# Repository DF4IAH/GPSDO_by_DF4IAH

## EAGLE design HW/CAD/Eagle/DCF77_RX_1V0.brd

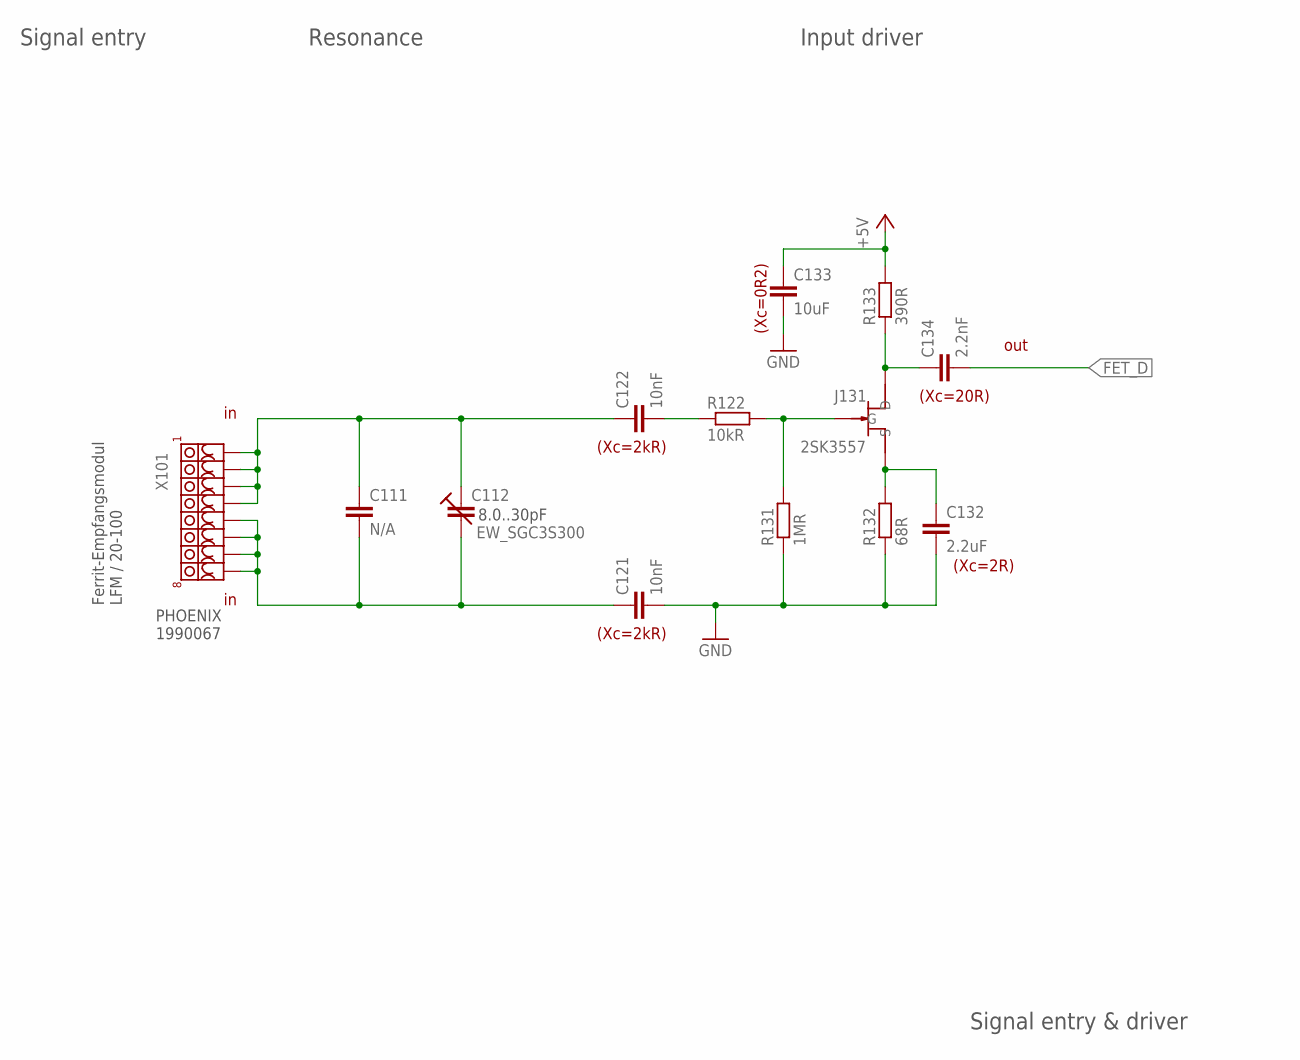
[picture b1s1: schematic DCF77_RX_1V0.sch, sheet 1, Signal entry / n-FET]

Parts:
C111: N/A; C0402
C112: EW_SGC3S300; 4MM5_X_3MM2__EW_SGC3S
C121, C122: 10nF; C0805
C132: 2.2uF; C0805
C133: 10uF; C0805
C134: 2.2nF; C0805
J131: 2SK3557; SOT23-3
R122: 10kR; R0805
R131: 1MR; R0805
R132: 68R; R0805
R133: 390R; R0805
X101: PHOENIX_1990067_1X8X2MM50_PTSA-0-5

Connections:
+5V: C133.1, R133.2; also elsewhere on the board
FET_D: C134.2; also elsewhere on the board
GND: C121.2, C132.2, C133.2, R131.1, R132.1; also elsewhere on the board
N101: C111.2, C112.CSTAT, C121.1, X101.5, X101.6, X101.7, X101.8
N102: C111.1, C112.CROT, C122.1, X101.1, X101.2, X101.3, X101.4
N122: C122.2, R122.1
N131: J131.P$3 (G), R122.2, R131.2
N132: C132.1, J131.P$1 (S), R132.2
N133: C134.1, J131.P$2 (D), R133.1

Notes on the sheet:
Signal entry & driver
Signal entry
out
Ferrit-Empfangsmodul LFM / 20-100
8.0..30pF
PHOENIX 1990067
Input driver
Resonance
(Xc=2R)
(Xc=20R)
(Xc=0R2)
(Xc=2kR)

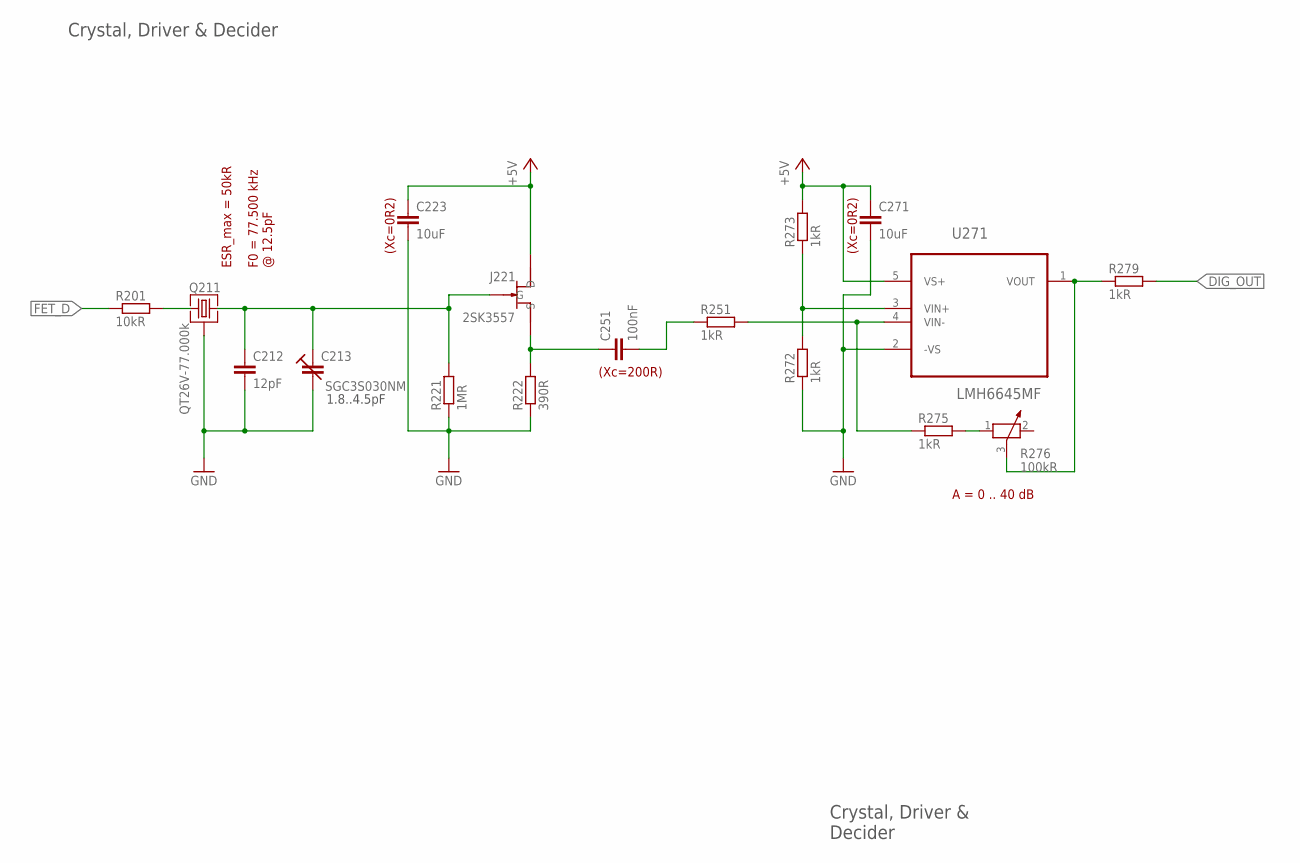
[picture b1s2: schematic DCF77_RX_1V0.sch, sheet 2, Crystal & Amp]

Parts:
C212: 12pF; C0402
C213: SGC3S030NM; 4MM5_X_3MM2__EW_SGC3S
C223, C271: 10uF; C0805
C251: 100nF; C0805
J221: 2SK3557; SOT23-3
Q211: QT26V-77.000k; QT26V_QST
R201: 10kR; R0805
R221: 1MR; R0805
R222: 390R; R0805
R251, R272, R273, R275, R279: 1kR; R0805
R276: 100kR; PT-10
U271: LMH6645MF; SOT-23-5

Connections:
+5V: C223.1, C271.1, J221.P$2 (D), R273.2, U271.5 (VS+); also elsewhere on the board
DIG_OUT: R279.2; also elsewhere on the board
FET_D: R201.1; also elsewhere on the board
GND: C212.2, C213.CSTAT, C223.2, C271.2, Q211.3, Q211.4 (3), R221.1, R222.1, R272.1, U271.2 (-VS); also elsewhere on the board
N211: Q211.1, R201.2
N221: C212.1, C213.CROT, J221.P$3 (G), Q211.2, R221.2
N222: C251.1, J221.P$1 (S), R222.2
N251: C251.2, R251.1
N271: R276.3, R279.1, U271.1 (VOUT)
N272: R272.2, R273.1, U271.3 (VIN+)
N273: R251.2, R275.1, U271.4 (VIN-)
N275: R275.2, R276.1

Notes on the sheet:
Crystal, Driver & Decider
1.8..4.5pF
Crystal, Driver & Decider
A = 0 .. 40 dB
ESR_max = 50kR
F0 = 77.500 kHz @ 12.5pF
(Xc=0R2)
(Xc=200R)

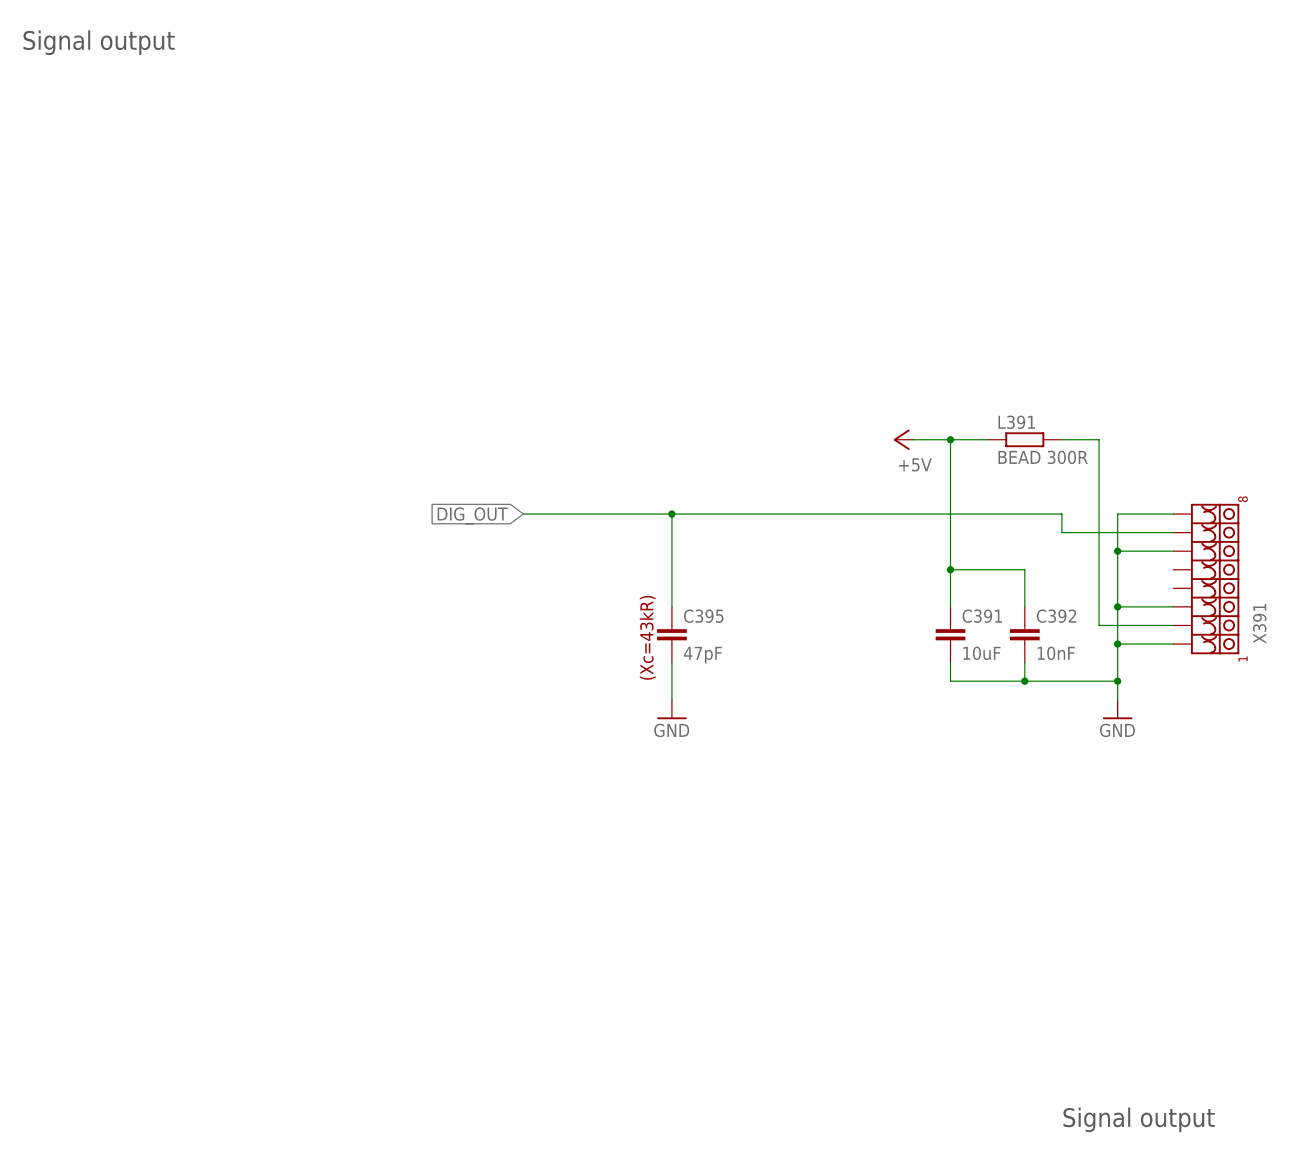
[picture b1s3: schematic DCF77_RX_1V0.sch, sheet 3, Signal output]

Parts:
C391: 10uF; C0805
C392: 10nF; C0805
C395: 47pF; C0805
L391: BEAD 300R; R1206
X391: PHOENIX_1990067_1X8X2MM50_PTSA-0-5

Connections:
+5V: C391.1, C392.1, L391.1; also elsewhere on the board
DIG_OUT: C395.1, X391.7; also elsewhere on the board
GND: C391.2, C392.2, C395.2, X391.1, X391.3, X391.6, X391.8; also elsewhere on the board
N391: L391.2, X391.2

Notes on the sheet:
Signal output
(Xc=43kR)

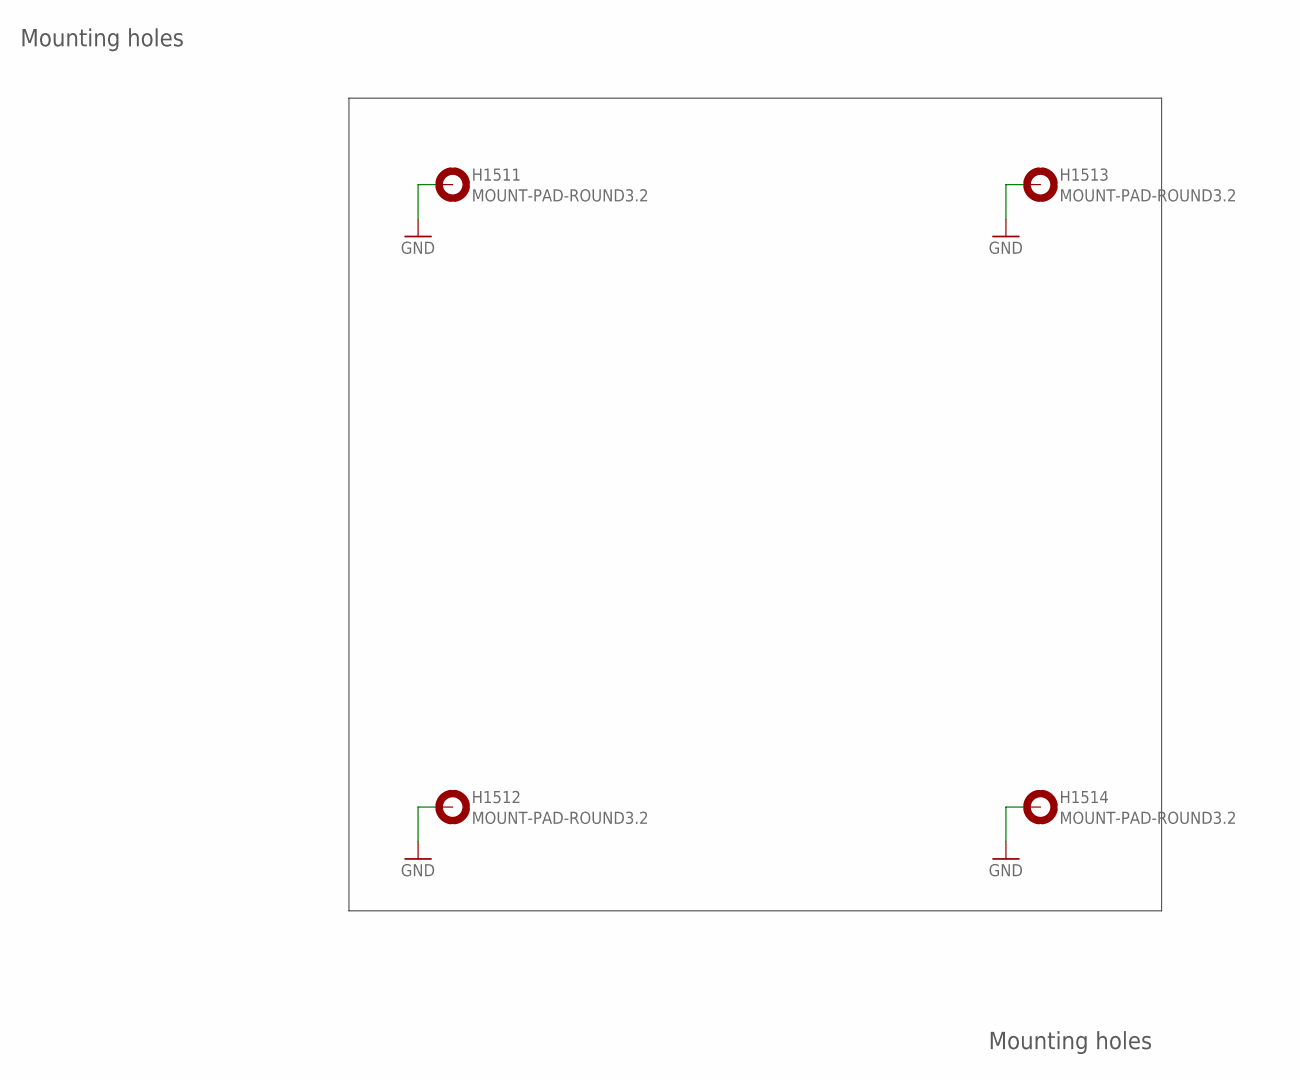
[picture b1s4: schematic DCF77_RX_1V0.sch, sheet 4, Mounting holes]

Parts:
H1511, H1512, H1513, H1514: MOUNT-PAD-ROUND3.2; 3,2-PAD

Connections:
GND: H1511.B3,2, H1512.B3,2, H1513.B3,2, H1514.B3,2; also elsewhere on the board

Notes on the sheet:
Mounting holes

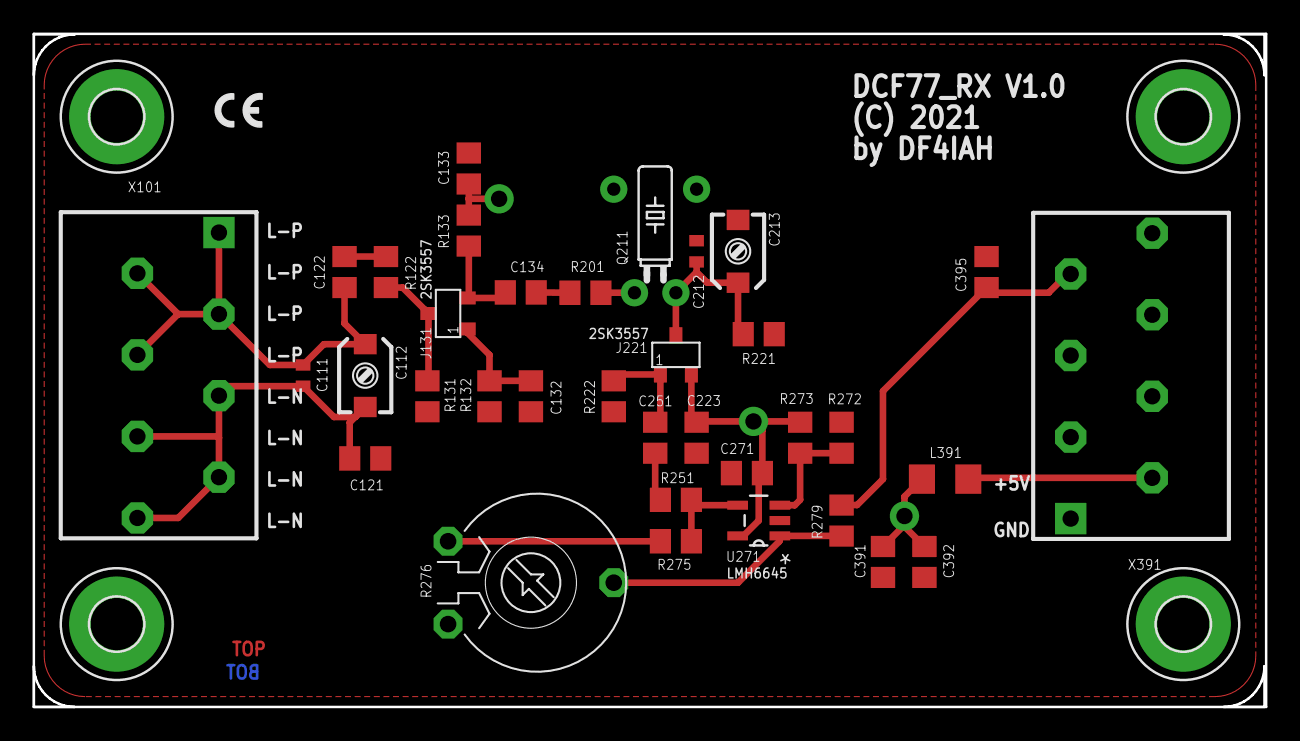
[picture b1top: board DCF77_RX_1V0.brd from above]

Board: 2 copper layers, 75.6 x 41.3 mm, 39 parts (0 on the bottom side), 19 nets.

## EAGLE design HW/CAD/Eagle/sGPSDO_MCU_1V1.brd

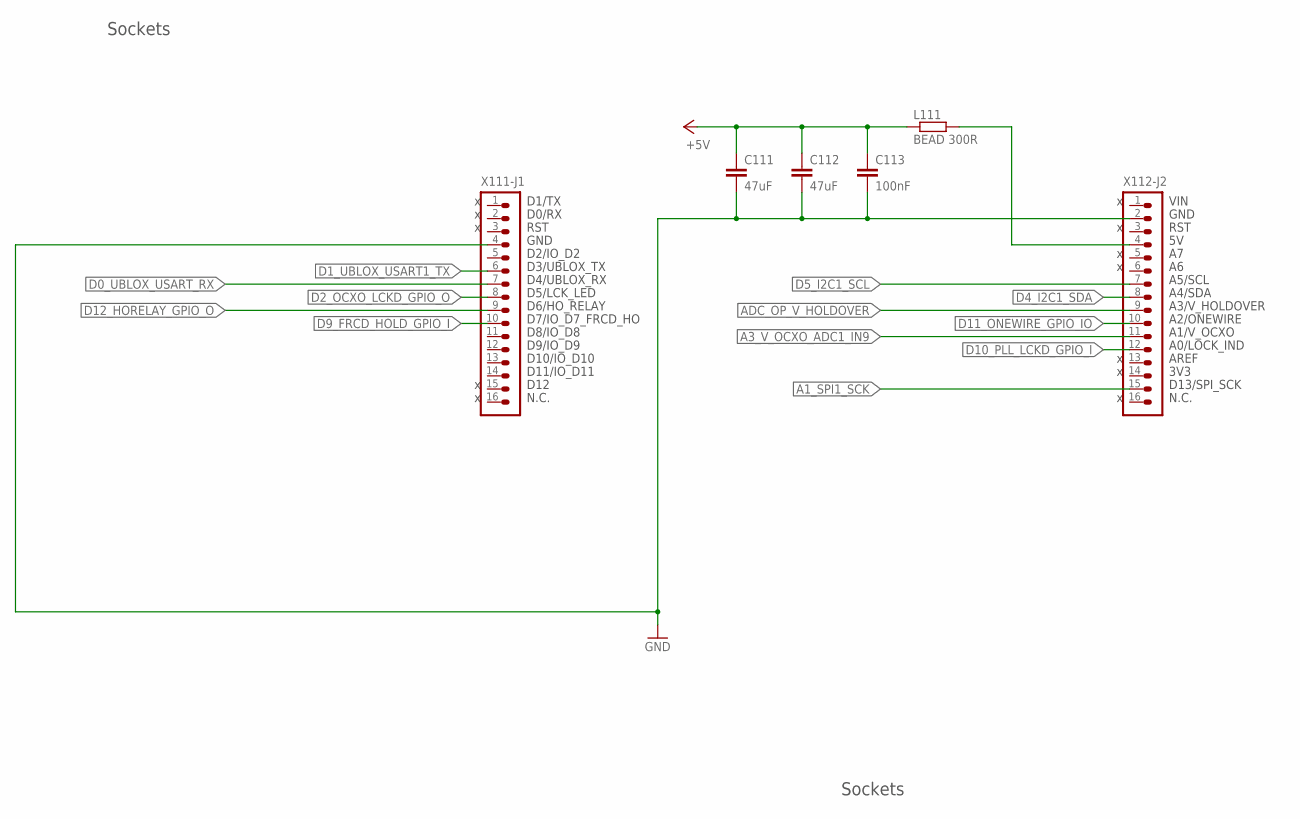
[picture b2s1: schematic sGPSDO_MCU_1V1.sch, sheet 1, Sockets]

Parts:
C111, C112: 47uF; C0805
C113: 100nF; C0805
L111: BEAD 300R; R1206
X111-J1, X112-J2: HEADER-1X16; 1X16

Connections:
+5V: C111.1, C112.1, C113.1, L111.1; also elsewhere on the board
A1_SPI1_SCK: X112-J2.15; also elsewhere on the board
A3_V_OCXO_ADC1_IN9: X112-J2.11; also elsewhere on the board
ADC_OP_V_HOLDOVER: X112-J2.9; also elsewhere on the board
D0_UBLOX_USART_RX: X111-J1.7; also elsewhere on the board
D1_UBLOX_USART1_TX: X111-J1.6; also elsewhere on the board
D2_OCXO_LCKD_GPIO_O: X111-J1.8; also elsewhere on the board
D4_I2C1_SDA: X112-J2.8; also elsewhere on the board
D5_I2C1_SCL: X112-J2.7; also elsewhere on the board
D9_FRCD_HOLD_GPIO_I: X111-J1.10; also elsewhere on the board
D10_PLL_LCKD_GPIO_I: X112-J2.12; also elsewhere on the board
D11_ONEWIRE_GPIO_IO: X112-J2.10; also elsewhere on the board
D12_HORELAY_GPIO_O: X111-J1.9; also elsewhere on the board
GND: C111.2, C112.2, C113.2, X111-J1.4, X112-J2.2; also elsewhere on the board
N112: L111.2, X112-J2.4

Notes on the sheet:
Sockets
A0/LOCK_IND
AREF
3V3
D13/SPI_SCK
N.C.
A1/V_OCXO
A2/ONEWIRE
A3/V_HOLDOVER
A4/SDA
A5/SCL
RST
GND
VIN
D12
D11/IO_D11
D10/IO_D10
D9/IO_D9
D8/IO_D8
D7/IO_D7_FRCD_HO
D6/HO_RELAY
D5/LCK_LED
D4/UBLOX_RX
D3/UBLOX_TX
D2/IO_D2
D0/RX
D1/TX

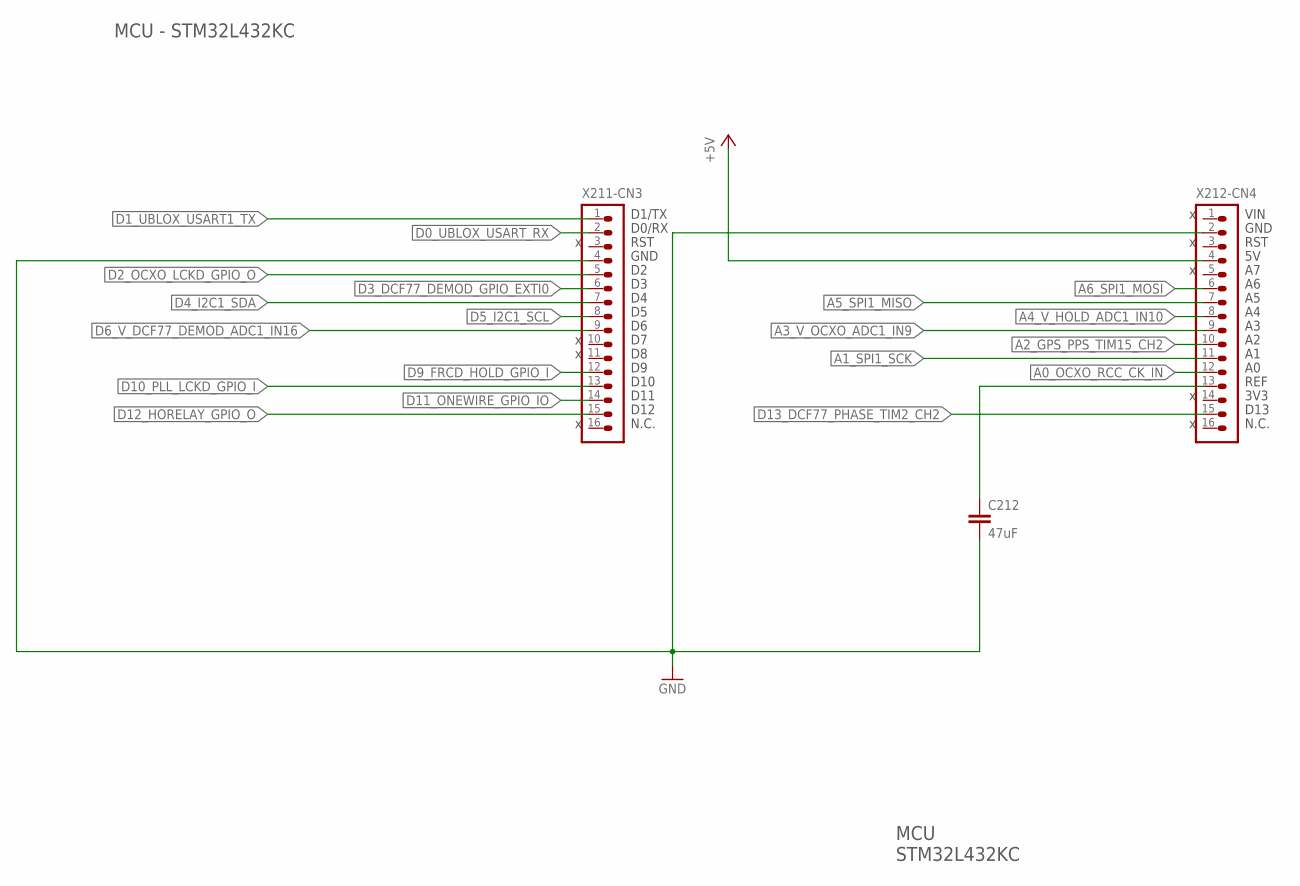
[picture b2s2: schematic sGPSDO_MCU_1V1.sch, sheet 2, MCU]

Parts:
C212: 47uF; C0805
X211-CN3, X212-CN4: HEADER-1X16; 1X16

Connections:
+5V: X212-CN4.4; also elsewhere on the board
A0_OCXO_RCC_CK_IN: X212-CN4.12; also elsewhere on the board
A1_SPI1_SCK: X212-CN4.11; also elsewhere on the board
A2_GPS_PPS_TIM15_CH2: X212-CN4.10; also elsewhere on the board
A3_V_OCXO_ADC1_IN9: X212-CN4.9; also elsewhere on the board
A4_V_HOLD_ADC1_IN10: X212-CN4.8; also elsewhere on the board
A5_SPI1_MISO: X212-CN4.7; also elsewhere on the board
A6_SPI1_MOSI: X212-CN4.6; also elsewhere on the board
D0_UBLOX_USART_RX: X211-CN3.2; also elsewhere on the board
D1_UBLOX_USART1_TX: X211-CN3.1; also elsewhere on the board
D2_OCXO_LCKD_GPIO_O: X211-CN3.5; also elsewhere on the board
D3_DCF77_DEMOD_GPIO_EXTI0: X211-CN3.6; also elsewhere on the board
D4_I2C1_SDA: X211-CN3.7; also elsewhere on the board
D5_I2C1_SCL: X211-CN3.8; also elsewhere on the board
D6_V_DCF77_DEMOD_ADC1_IN16: X211-CN3.9; also elsewhere on the board
D9_FRCD_HOLD_GPIO_I: X211-CN3.12; also elsewhere on the board
D10_PLL_LCKD_GPIO_I: X211-CN3.13; also elsewhere on the board
D11_ONEWIRE_GPIO_IO: X211-CN3.14; also elsewhere on the board
D12_HORELAY_GPIO_O: X211-CN3.15; also elsewhere on the board
D13_DCF77_PHASE_TIM2_CH2: X212-CN4.15; also elsewhere on the board
GND: C212.2, X211-CN3.4, X212-CN4.2; also elsewhere on the board
VREF: C212.1, X212-CN4.13

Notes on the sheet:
MCU - STM32L432KC
MCU STM32L432KC
REF
3V3
D13
N.C.
RST
GND
VIN
D12
D11
D10
D0/RX
D1/TX

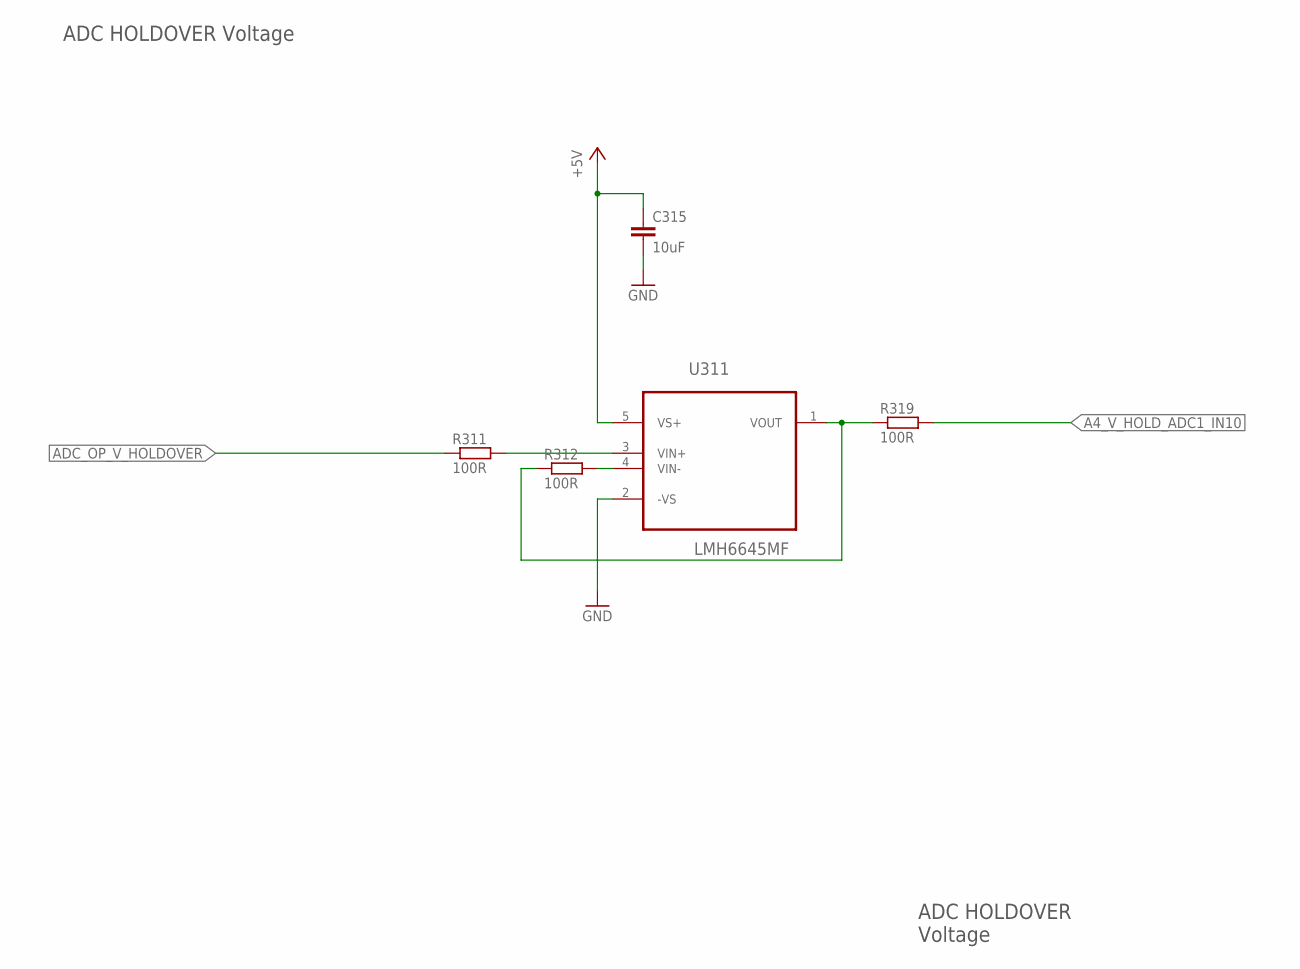
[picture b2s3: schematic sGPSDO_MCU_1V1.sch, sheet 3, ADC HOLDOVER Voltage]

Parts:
C315: 10uF; C0805
R311, R312, R319: 100R; R0805
U311: LMH6645MF; SOT-23-5

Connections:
+5V: C315.1, U311.5 (VS+); also elsewhere on the board
A4_V_HOLD_ADC1_IN10: R319.2; also elsewhere on the board
ADC_OP_V_HOLDOVER: R311.1; also elsewhere on the board
GND: C315.2, U311.2 (-VS); also elsewhere on the board
N311: R311.2, U311.3 (VIN+)
N312: R312.2, U311.4 (VIN-)
N319: R312.1, R319.1, U311.1 (VOUT)

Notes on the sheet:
ADC HOLDOVER Voltage
ADC HOLDOVER Voltage

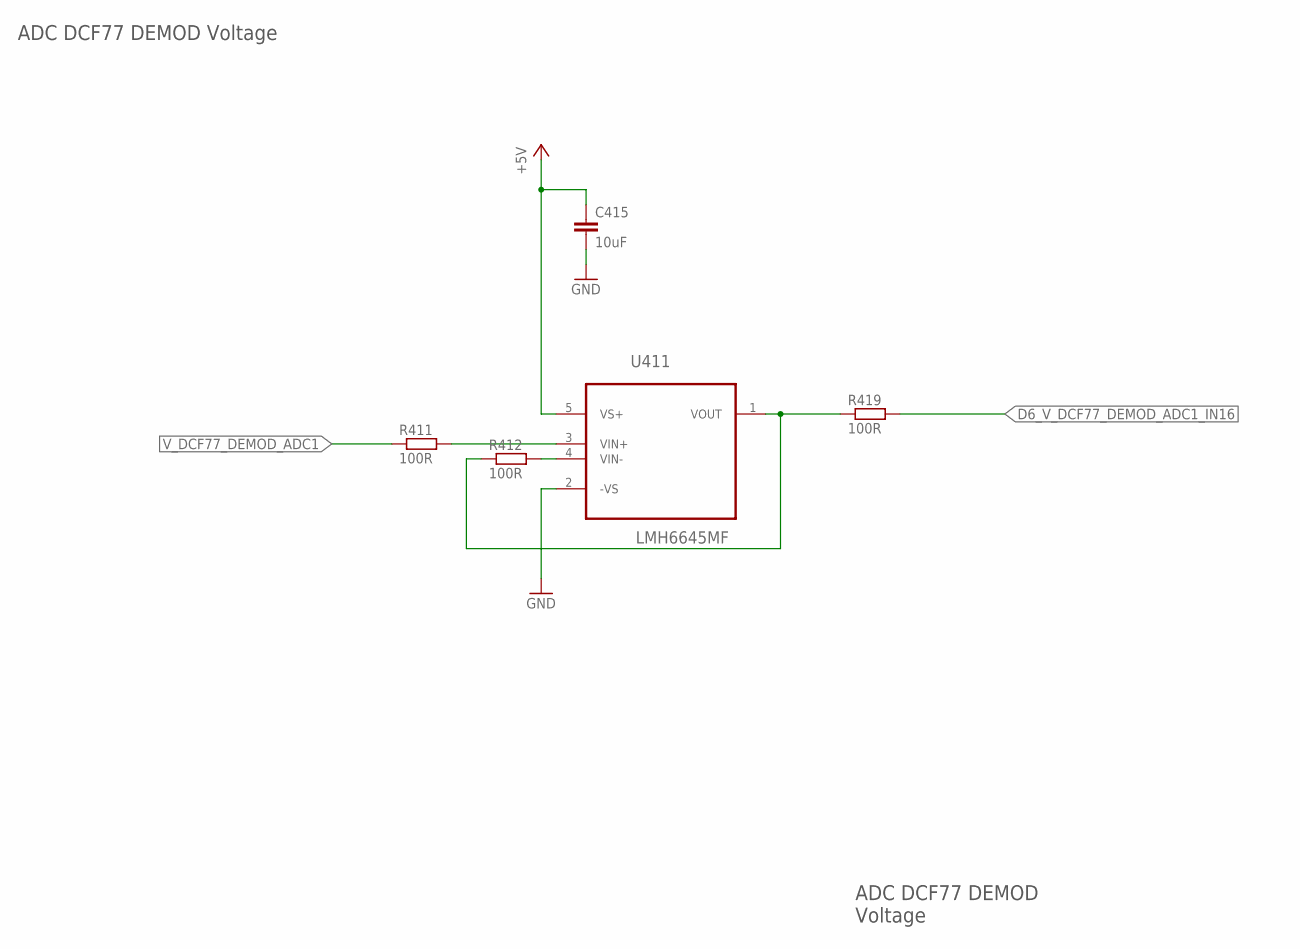
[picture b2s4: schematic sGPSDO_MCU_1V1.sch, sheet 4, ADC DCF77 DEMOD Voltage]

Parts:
C415: 10uF; C0805
R411, R412, R419: 100R; R0805
U411: LMH6645MF; SOT-23-5

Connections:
+5V: C415.1, U411.5 (VS+); also elsewhere on the board
D6_V_DCF77_DEMOD_ADC1_IN16: R419.2; also elsewhere on the board
GND: C415.2, U411.2 (-VS); also elsewhere on the board
N411: R411.2, U411.3 (VIN+)
N412: R412.2, U411.4 (VIN-)
N419: R412.1, R419.1, U411.1 (VOUT)
V_DCF77_DEMOD_ADC1: R411.1; also elsewhere on the board

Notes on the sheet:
ADC DCF77 DEMOD Voltage
ADC DCF77 DEMOD Voltage

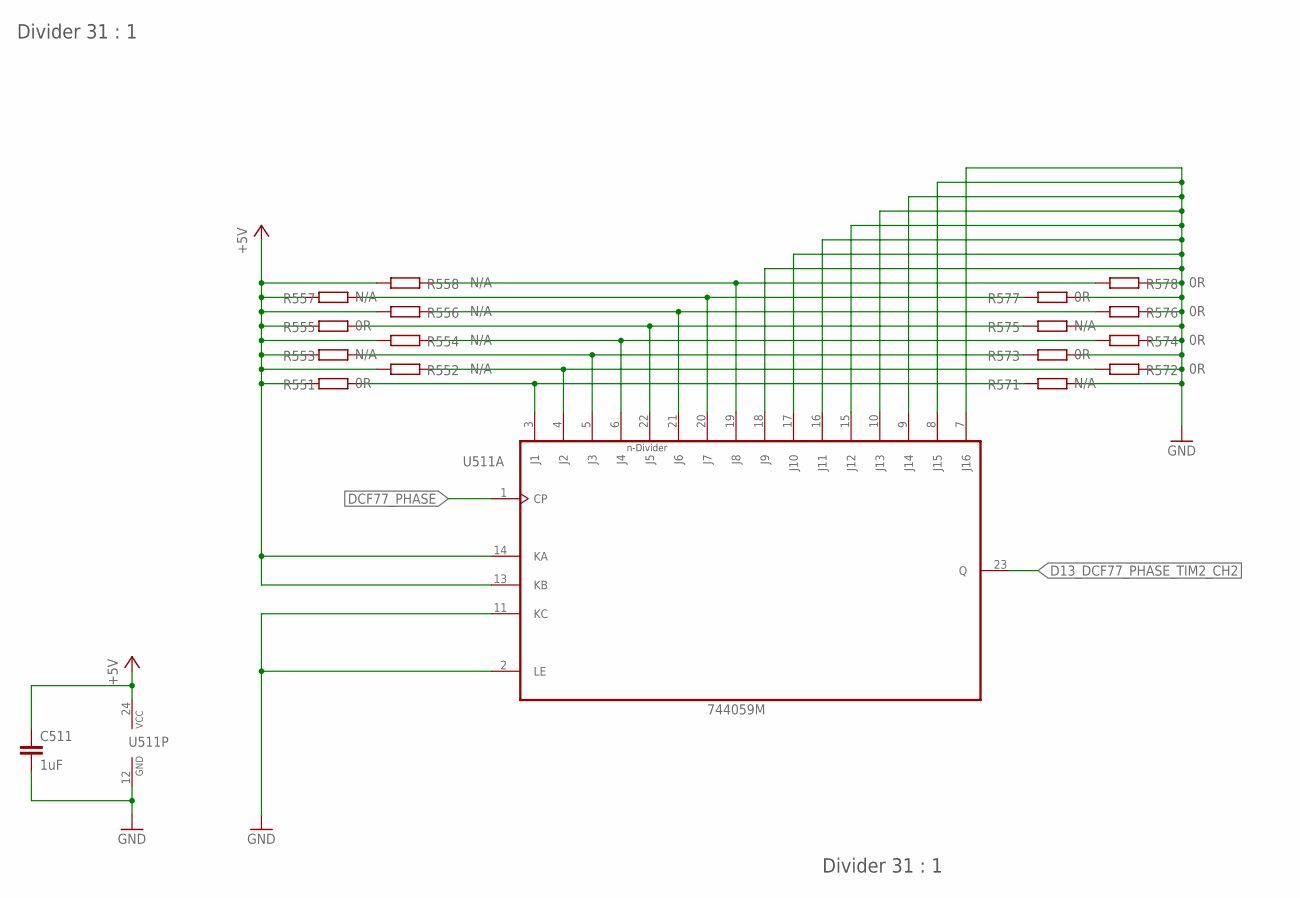
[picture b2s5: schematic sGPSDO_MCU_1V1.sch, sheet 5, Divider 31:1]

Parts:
C511: 1uF; C0805
R551, R555, R572, R573, R574, R576, R577, R578: 0R; R0402
R552, R553, R554, R556, R557, R558, R571, R575: N/A; R0402
U511: 744059M; SOIC24

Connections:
+5V: C511.1, R551.1, R552.1, R553.1, R554.1, R555.1, R556.1, R557.1, R558.1, U511.13 (KB), U511.14 (KA), U511.24 (VCC); also elsewhere on the board
D13_DCF77_PHASE_TIM2_CH2: U511.23 (Q); also elsewhere on the board
DCF77_PHASE: U511.1 (CP); also elsewhere on the board
GND: C511.2, R571.2, R572.2, R573.2, R574.2, R575.2, R576.2, R577.2, R578.2, U511.2 (LE), U511.7 (J16), U511.8 (J15), U511.9 (J14), U511.10 (J13), U511.11 (KC), U511.12 (GND), U511.15 (J12), U511.16 (J11), U511.17 (J10), U511.18 (J9); also elsewhere on the board
N551: R551.2, R571.1, U511.3 (J1)
N552: R552.2, R572.1, U511.4 (J2)
N553: R553.2, R573.1, U511.5 (J3)
N554: R554.2, R574.1, U511.6 (J4)
N555: R555.2, R575.1, U511.22 (J5)
N556: R556.2, R576.1, U511.21 (J6)
N557: R557.2, R577.1, U511.20 (J7)
N558: R558.2, R578.1, U511.19 (J8)

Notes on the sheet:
Divider 31 : 1

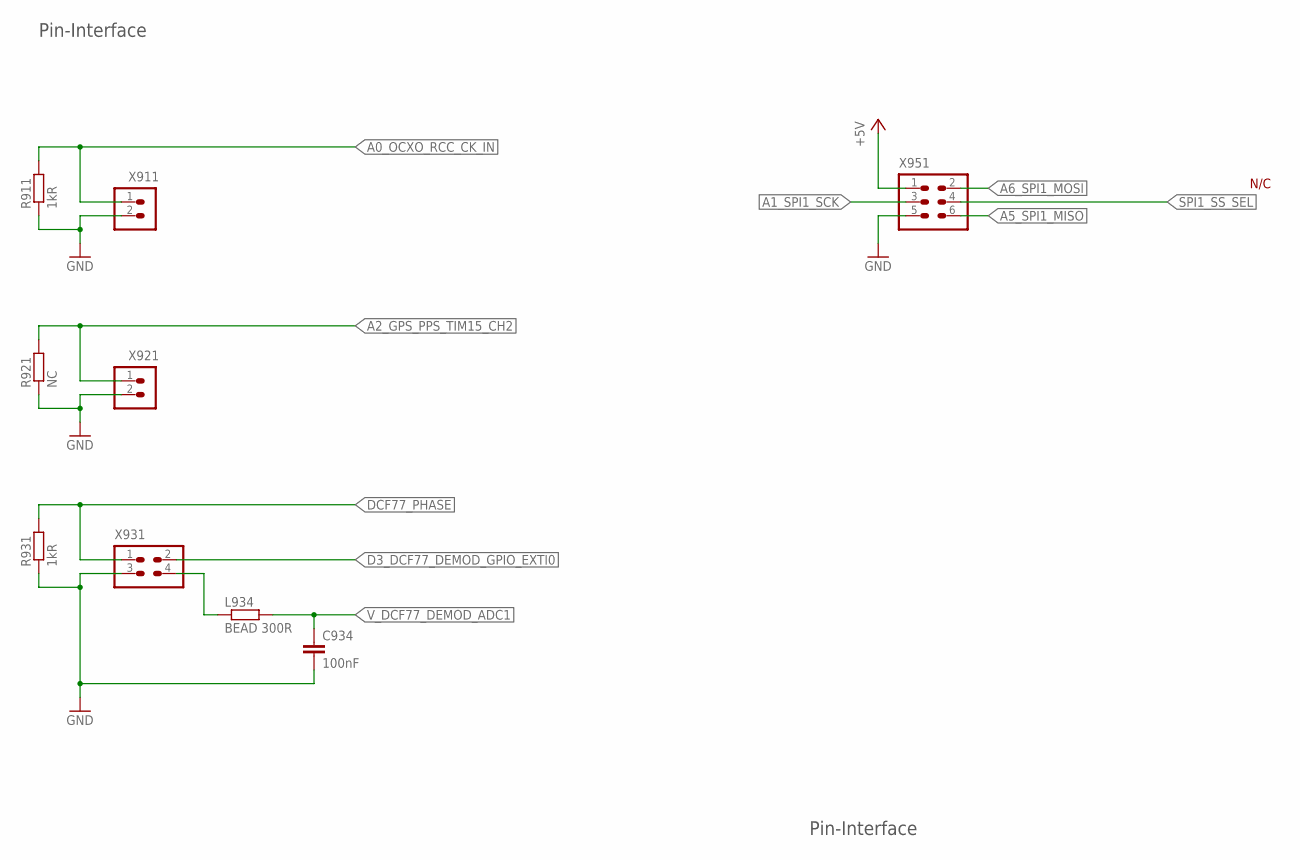
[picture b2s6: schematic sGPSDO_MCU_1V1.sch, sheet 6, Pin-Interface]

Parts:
C934: 100nF; C0805
L934: BEAD 300R; R1206
R911, R931: 1kR; R0805
R921: NC; R0805
X911, X921: HEADER-1X2; 1X02
X931: HEADER-2X2; 2X02
X951: HEADER-2X3; 2X03

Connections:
+5V: X951.1; also elsewhere on the board
A0_OCXO_RCC_CK_IN: R911.2, X911.1; also elsewhere on the board
A1_SPI1_SCK: X951.3; also elsewhere on the board
A2_GPS_PPS_TIM15_CH2: R921.2, X921.1; also elsewhere on the board
A5_SPI1_MISO: X951.6; also elsewhere on the board
A6_SPI1_MOSI: X951.2; also elsewhere on the board
D3_DCF77_DEMOD_GPIO_EXTI0: X931.2; also elsewhere on the board
DCF77_PHASE: R931.2, X931.1; also elsewhere on the board
GND: C934.2, R911.1, R921.1, R931.1, X911.2, X921.2, X931.3, X951.5; also elsewhere on the board
N934: L934.1, X931.4
SPI1_SS_SEL: X951.4
V_DCF77_DEMOD_ADC1: C934.1, L934.2; also elsewhere on the board

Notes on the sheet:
Pin-Interface
N/C

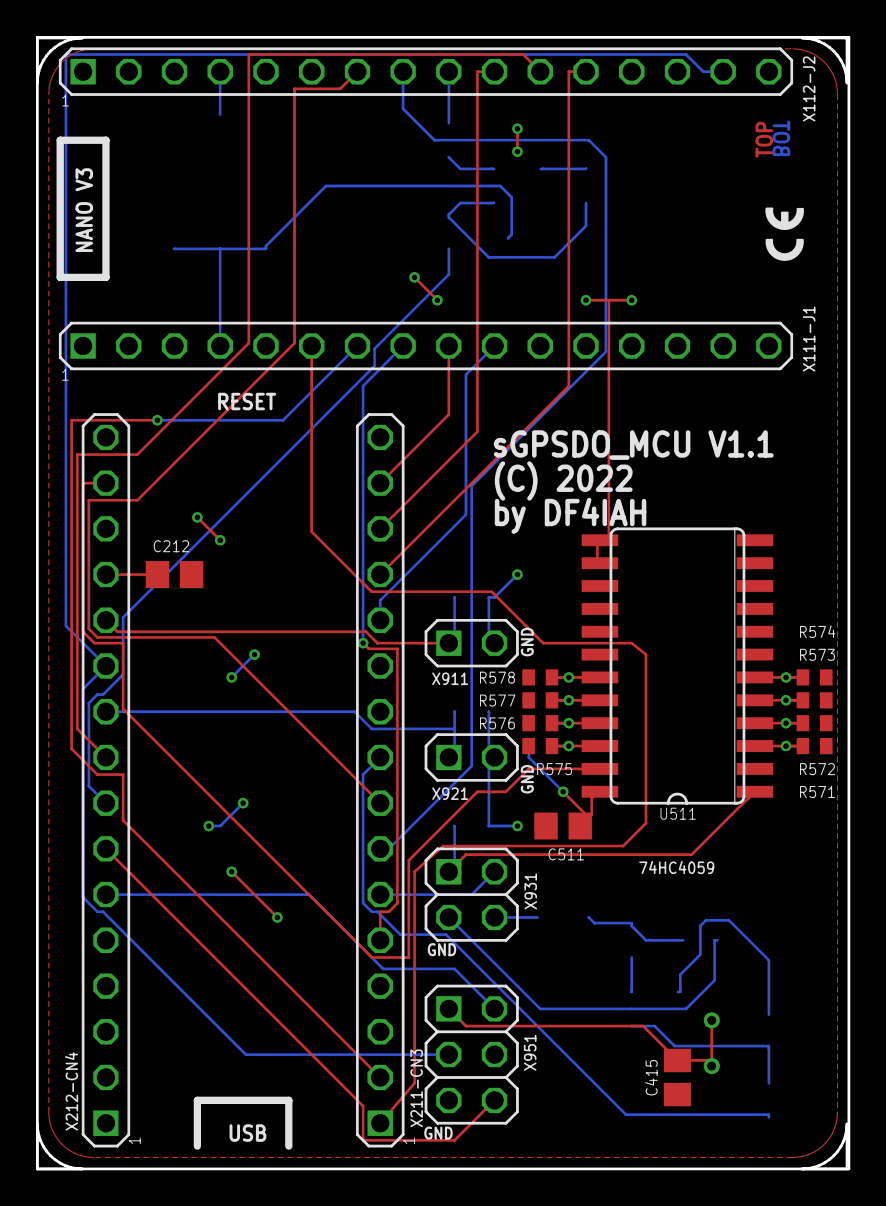
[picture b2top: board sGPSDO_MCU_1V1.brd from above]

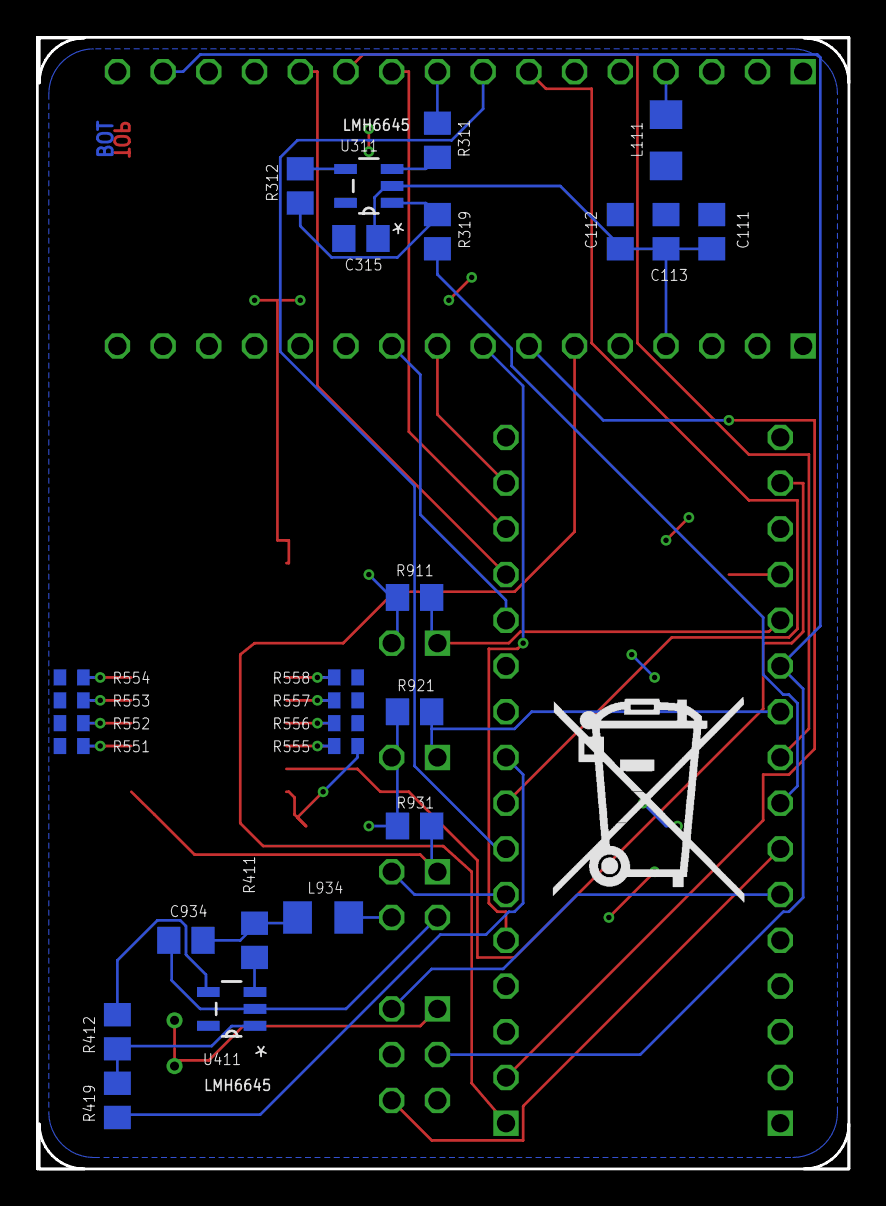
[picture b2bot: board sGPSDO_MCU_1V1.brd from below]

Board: 2 copper layers, 45.1 x 62.9 mm, 46 parts (26 on the bottom side), 41 nets.

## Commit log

2022-07-01 HW - Eagle - sGPSDO_MCU V1.0 - no DCF77 possible due to bad package size of divider
2022-07-01 HW - Eagle - sGPSDO_MCU V1.1 - divider package changed from 150 mil to 300 mil
2022-07-01 HW - Eagle - DCF77_RX_1V0 - value tweaks done

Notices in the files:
HW/CAD/Eagle/DCF77_RX_1V0.brd:
(C) 2021
HW/CAD/Eagle/sGPSDO_MCU_1V1.brd:
(C) 2022
